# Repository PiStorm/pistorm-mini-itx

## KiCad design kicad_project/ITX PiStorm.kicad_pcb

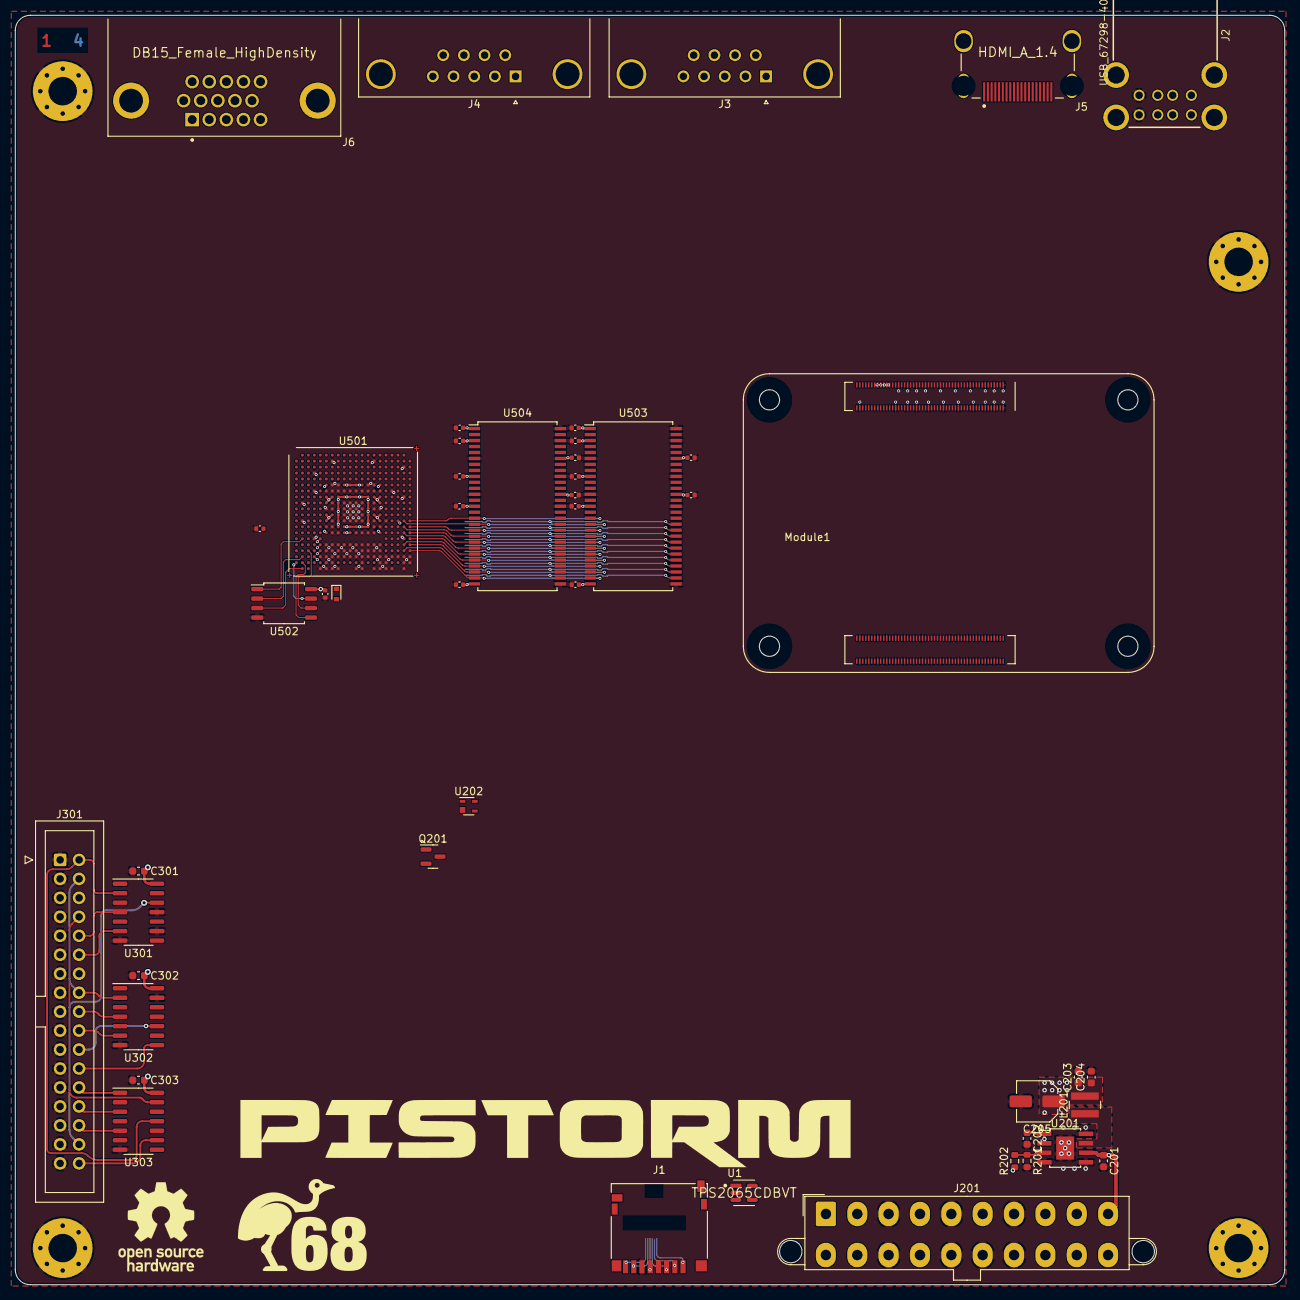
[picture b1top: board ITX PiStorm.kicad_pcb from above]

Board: 4 copper layers, 170.0 x 170.0 mm, 52 parts (0 on the bottom side), 55 nets.

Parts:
C201: 10µ; C_0603_1608Metric
C202, C301, C302, C303: 100nF; C_0603_1608Metric
C203, C204: 22µ; C_0603_1608Metric
C205: 100µ; CP_Elec_5x5.9
C501, C502, C503, C504, C505, C506, C507, C508, C509, C510, C511, C512, C513, C514, C515, C516: 100nF; C_0402_1005Metric
D501: 1N4148WT; D_SOD-523
H1, H2, H3, H4: MountingHole_Pad; MountingHole_4mm_Pad_Via
J1: Micro_SD_Card_Det; microSD_HC_Hirose_DM3D-SF
J2: USB_67298-4090; MOLEX_USB_67298-4090
J3, J4: DB9_Male_MountingHoles; DSUB-9_Male_Horizontal_P2.77x2.84mm_EdgePinOffset4.94mm_Hou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
J5: HDMI_A_1.4; Wurth-685119134923-MFG
J6: DB15_Female_HighDensity; TE-1-1734530-1-0-0-0
J201: ATX-20; Molex_Mini-Fit_Jr_5566-20A2_2x10_P4.20mm_Vertical
J301: Conn_02x17_Odd_Even; IDC-Header_2x17_P2.54mm_Vertical
L201: 2.2µ; L_Wuerth_MAPI-4030
Module1: ComputeModule4-CM4; Raspberry-Pi-4-Compute-Module
Q201: DMG2301L; SOT-23
R201: 20k; R_0603_1608Metric
R202: 7k5; R_0603_1608Metric
U1: TPS2065CDBVT; Texas_Instruments-DBV0005A-0-0-IPC_B
U201: ST1S10PHR; TI_SO-PowerPAD-8
U202: ADCMP350; Analog_KS-4
U301, U302: 74LVC06; SO-14_3.9x8.65mm_P1.27mm
U303: 74LVC14; SO-14_3.9x8.65mm_P1.27mm
U501: LFE5U-85F-6BG381x; Lattice_caBGA-381_17.0x17.0mm_Layout20x20_P0.8mm_Ball0.4mm_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
U502: W25Q128JVS; SOIC-8_5.23x5.23mm_P1.27mm
U503, U504: MT48LC16M16A2P; TSOP-II-54_22.2x10.16mm_P0.8mm

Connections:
+1V1: C203.1, C204.1, C205.1, L201.2, R202.1, U501.H8 (VCC), U501.H9 (VCC), U501.H10 (VCC), U501.H11 (VCC), U501.H12 (VCC), U501.H13 (VCC), U501.J8 (VCC), U501.J13 (VCC), U501.K8 (VCC), U501.K13 (VCC), U501.L8 (VCC), U501.L13 (VCC), U501.M8 (VCC), U501.M13 (VCC), U501.N8 (VCC), U501.N9 (VCC), U501.N10 (VCC), U501.N11 (VCC), U501.N12 (VCC), U501.N13 (VCC)
+2V5: D501.1 (K), U501.F6 (VCCAUX), U501.F15 (VCCAUX), U501.P6 (VCCAUX), U501.P15 (VCCAUX)
+3V3: C301.1, C302.1, C303.1, C501.1, C502.1, C503.1, C504.1, C505.1, C506.1, C507.1, C508.1, C509.1, C510.1, C511.1, C512.1, C513.1, C514.1, C515.1, C516.1, D501.2 (A), J201.1 (+3.3V), J201.2 (+3.3V), J201.11 (+3.3V), U301.14 (VCC), U302.14 (VCC), U303.14 (VCC), U501.F9 (VCCIO0), U501.F10 (VCCIO0), U501.F11 (VCCIO1), U501.F12 (VCCIO1), U501.H6 (VCCIO7), U501.H7 (VCCIO7), U501.H14 (VCCIO2), U501.H15 (VCCIO2), U501.J6 (VCCIO7), U501.J15 (VCCIO2), U501.L6 (VCCIO6), U501.L7 (VCCIO6), U501.L14 (VCCIO3), U501.L15 (VCCIO3), U501.M6 (VCCIO6), U501.M15 (VCCIO3), U501.P9 (VCCIO8), U501.P10 (VCCIO8), U501.T4 (CFG_1), U502.8 (VCC), U503.1 (VDD), U503.3 (VDDQ), U503.9 (VDDQ), U503.14 (VDD), U503.27 (VDD), U503.43 (VDDQ), U503.49 (VDDQ), U504.1 (VDD), U504.3 (VDDQ), U504.9 (VDDQ), U504.14 (VDD), U504.27 (VDD), U504.43 (VDDQ), U504.49 (VDDQ)
+5V: J201.4 (+5V), J201.6 (+5V), J201.19 (+5V), J201.20 (+5V), Module1.77 (+5v_(Input)), Module1.79 (+5v_(Input)), Module1.81 (+5v_(Input)), Module1.83 (+5v_(Input)), Module1.85 (+5v_(Input)), Module1.87 (+5v_(Input))
+12V: C201.1, C202.1, J201.10 (+12V), U201.1 (VINA), U201.2 (INH), U201.6 (VINSW)
/CM4 Board/SD_CLK: J1.5 (CLK), Module1.57 (SD_CLK)
/CM4 Board/SD_CMD: J1.3 (CMD), Module1.62 (SD_CMD)
/CM4 Board/SD_DAT0: J1.7 (DAT0), Module1.63 (SD_DAT0)
/CM4 Board/SD_DAT1: J1.8 (DAT1), Module1.67 (SD_DAT1)
/CM4 Board/SD_DAT2: J1.1 (DAT2), Module1.69 (SD_DAT2)
/CM4 Board/SD_DAT3: J1.2 (DAT3/CD), Module1.61 (SD_DAT3)
/Floppy Interface/~DIR: J301.18, U302.4
/Floppy Interface/~DS1: J301.10, U301.4
/Floppy Interface/~DS2: J301.12, U301.6
/Floppy Interface/~DSKCHG: J301.34, U303.9
/Floppy Interface/~INDEX: J301.8, U303.13
/Floppy Interface/~MTRON: J301.4, J301.16, U302.2
/Floppy Interface/~RDATA: J301.30, U303.5
/Floppy Interface/~REDWC: J301.2, U301.2, U303.11
/Floppy Interface/~SIDE1: J301.32, U301.12
/Floppy Interface/~STEP: J301.20, U302.6
/Floppy Interface/~TRK00: J301.26, U303.1
/Floppy Interface/~WDATA: J301.22, U302.10
/Floppy Interface/~WGATE: J301.24, U302.8
/Floppy Interface/~WPT: J301.28, U303.3
/Memory and Bus Interface/A0: U501.T19 (PR89A), U503.23 (A0), U504.23 (A0)
/Memory and Bus Interface/A1: U501.T20 (PR86C), U503.24 (A1), U504.24 (A1)
/Memory and Bus Interface/A2: U501.U19 (PR89C), U503.25 (A2), U504.25 (A2)
/Memory and Bus Interface/A3: U501.U20 (PR86D), U503.26 (A3), U504.26 (A3)
/Memory and Bus Interface/A4: U503.29 (A4), U504.29 (A4)
/Memory and Bus Interface/A5: U503.30 (A5), U504.30 (A5)
/Memory and Bus Interface/A6: U503.31 (A6), U504.31 (A6)
/Memory and Bus Interface/A7: U503.32 (A7), U504.32 (A7)
/Memory and Bus Interface/A8: U503.33 (A8), U504.33 (A8)
/Memory and Bus Interface/A9: U503.34 (A9), U504.34 (A9)
/Memory and Bus Interface/A10: U501.R20 (PR86B), U503.22 (A10), U504.22 (A10)
/Memory and Bus Interface/A11: U503.35 (A11), U504.35 (A11)
/Memory and Bus Interface/A12: U503.36 (A12), U504.36 (A12)
/Memory and Bus Interface/BA0: U501.P20 (PR86A), U503.20 (BA0), U504.20 (BA0)
/Memory and Bus Interface/BA1: U501.P19 (PR83C), U503.21 (BA1), U504.21 (BA1)
/Memory and Bus Interface/CKE: U503.37 (CKE), U504.37 (CKE)
/Memory and Bus Interface/CLK: U503.38 (CLK), U504.38 (CLK)
/Memory and Bus Interface/~CAS: U501.M19 (PR47D), U503.17 (~CAS), U504.17 (~CAS)
/Memory and Bus Interface/~CS: U501.N19 (PR83A), U503.19 (~CS), U504.19 (~CS)
/Memory and Bus Interface/~RAS: U501.N20 (PR83B), U503.18 (~RAS), U504.18 (~RAS)
/Memory and Bus Interface/~WE: U501.M20 (PR47B), U503.16 (~WE), U504.16 (~WE)
GND: C201.2, C202.2, C203.2, C204.2, C205.2, C301.2, C302.2, C303.2, C501.2, C502.2, C503.2, C504.2, C505.2, C506.2, C507.2, C508.2, C509.2, C510.2, C511.2, C512.2, C513.2, C514.2, C515.2, C516.2, H1.1, H2.1, H3.1, H4.1, J1.6 (VSS), J2.4 (GND`), J2.8 (GND), J201.3 (GND), J201.5 (GND), J201.7 (GND), J201.13 (GND), J201.15 (GND), J201.16 (GND), J201.17 (GND), J301.1, J301.3, J301.5, J301.7, J301.9, J301.11, J301.13, J301.15, J301.17, J301.19, J301.21, J301.23, J301.25, J301.27, J301.29, J301.31, J301.33, Module1.1 (GND), Module1.2 (GND), Module1.7 (GND), Module1.8 (GND), Module1.13 (GND), Module1.14 (GND), Module1.22 (GND), Module1.23 (GND), Module1.32 (GND), Module1.33 (GND), Module1.42 (GND), Module1.43 (GND), Module1.52 (GND), Module1.53 (GND), Module1.59 (GND), Module1.60 (GND), Module1.65 (GND), Module1.66 (GND), Module1.71 (GND), Module1.74 (GND), Module1.98 (GND), Module1.107 (GND), Module1.108 (GND), Module1.113 (GND), Module1.114 (GND), Module1.119 (GND), Module1.120 (GND), Module1.125 (GND), Module1.126 (GND), Module1.131 (GND), Module1.132 (GND), Module1.137 (GND), Module1.138 (GND), Module1.144 (GND), Module1.150 (GND), Module1.155 (GND), Module1.156 (GND), Module1.161 (GND), Module1.162 (GND), Module1.167 (GND), Module1.168 (GND), Module1.173 (GND), Module1.174 (GND), Module1.179 (GND), Module1.180 (GND), Module1.185 (GND), Module1.186 (GND), Module1.191 (GND), Module1.192 (GND), Module1.197 (GND), Module1.198 (GND), R201.2, U201.4 (AGND), U201.5 (SYNC), U201.8 (PGND), U201.9 (PADGND), U301.7 (GND), U301.9, U301.11, U302.7 (GND), U302.13, U303.7 (GND), U501.B7 (GND), U501.B14 (GND), U501.C19 (GND), U501.D4 (GND), U501.F7 (GND), U501.F8 (GND), U501.F13 (GND), U501.F14 (GND), U501.G4 (GND), U501.G6 (GND), U501.G7 (GND), U501.G8 (GND), U501.G9 (GND), U501.G10 (GND), U501.G11 (GND), U501.G12 (GND), U501.G13 (GND), U501.G14 (GND), U501.G15 (GND), U501.G17 (GND), U501.H19 (GND), U501.J2 (GND), U501.J7 (GND), U501.J9 (GND), U501.J10 (GND), U501.J11 (GND), U501.J12 (GND), U501.J14 (GND), U501.K6 (GND), U501.K7 (GND), U501.K9 (GND), U501.K10 (GND), U501.K11 (GND), U501.K12 (GND), U501.K14 (GND), U501.K15 (GND), U501.L9 (GND), U501.L10 (GND), U501.L11 (GND), U501.L12 (GND), U501.M2 (GND), U501.M7 (GND), U501.M9 (GND), U501.M10 (GND), U501.M11 (GND), U501.M12 (GND), U501.M14 (GND), U501.M16 (GND), U501.N6 (GND), U501.N7 (GND), U501.N14 (GND), U501.N15 (GND), U501.P7 (GND), U501.P8 (GND), U501.P11 (GND), U501.P12 (GND), U501.P13 (GND), U501.P14 (GND), U501.R4 (CFG_2), U501.R19 (GND), U501.T6 (GND), U501.T7 (GND), U501.T8 (GND), U501.T9 (GND), U501.T10 (GND), U501.T11 (GND), U501.T12 (GND), U501.T13 (GND), U501.T14 (GND), U501.T15 (GND), U501.U4 (CFG_0), U501.U6 (GND), U501.U7 (GND), U501.U8 (GND), U501.U9 (GND), U501.U10 (GND), U501.U11 (GND), U501.U12 (GND), U501.U13 (GND), U501.U14 (GND), U501.U15 (GND), U501.V5 (GND), U501.V6 (GND), U501.V7 (GND), U501.V8 (GND), U501.V9 (GND), U501.V10 (GND), U501.V11 (GND), U501.V12 (GND), U501.V13 (GND), U501.V14 (GND), U501.V15 (GND), U501.V16 (GND), U501.V17 (GND), U501.V18 (GND), U501.V19 (GND), U501.V20 (GND), U501.W6 (GND), U501.W7 (GND), U501.W12 (GND), U501.W15 (GND), U501.W16 (GND), U501.W19 (GND), U501.W20 (GND), U501.Y5 (GND), U501.Y6 (GND), U501.Y7 (GND), U501.Y8 (GND), U501.Y11 (GND), U501.Y12 (GND), U501.Y14 (GND), U501.Y15 (GND), U501.Y16 (GND), U501.Y17 (GND), U501.Y19 (GND), U502.4 (GND), U503.6 (VSSQ), U503.12 (VSSQ), U503.28 (VSS), U503.41 (VSS), U503.46 (VSSQ), U503.52 (VSSQ), U503.54 (VSS), U504.6 (VSSQ), U504.12 (VSSQ), U504.28 (VSS), U504.41 (VSS), U504.46 (VSSQ), U504.52 (VSSQ), U504.54 (VSS)
unnamed: L201.1, U201.7 (SW)
unnamed: R201.1, R202.2, U201.3 (FB)
unnamed: U501.R2 (PB15A), U502.1 (~CS)
unnamed: U501.U3 (CCLK), U502.6 (CLK)
unnamed: U501.V2 (PB11A), U502.2 (DO(IO1))
unnamed: U501.W1 (PB9A), U502.7 (IO3)
unnamed: U501.W2 (PB11B), U502.5 (DI(IO0))
unnamed: U501.Y2 (PB9B), U502.3 (IO2)

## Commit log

2022-04-06 git ignore file for kicad project
2022-04-07 Initial version, only board outline is valid
2022-04-19 playground start
2022-04-19 added ecp5 fpga without anything connected yet, added power to fpga
2022-04-29 added BGA 381 footprint 3d model
2022-04-29 added bits and pieces: a bit of memory, a bit of 1.1V power
2022-05-02 minor wip updates
2023-05-23 added git ignore file
2023-05-23 Wip commit
